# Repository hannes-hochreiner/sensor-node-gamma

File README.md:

# Sensor Node Gamma

## Core parts

### STM32
  * manufacturer: STMicroelectronics
  * manufacturer id: STM32L021K4T6
  * digi-key id: [497-17903-ND](https://www.digikey.de/product-detail/de/stmicroelectronics/STM32L021K4T6/497-17903-ND)
  * [datasheet](http://www.st.com/content/ccc/resource/technical/document/datasheet/86/a6/5f/95/33/50/4e/d6/DM00206858.pdf/files/DM00206858.pdf/jcr:content/translations/en.DM00206858.pdf)
  * sleep current: 0.54 µA
  * price: 1.87 EUR

### RFM98
  * manufacturer: Seeed Technology Co., Ltd
  * manufacturer id: 109990165
  * digi-key id: [1597-1491-ND](https://www.digikey.de/product-detail/de/seeed-technology-co-ltd/109990165/1597-1491-ND)
  * [datasheet](https://github.com/SeeedDocument/RFM95-98_LoRa_Module/blob/master/RFM95_96_97_98_DataSheet.pdf)
  * sleep current: 0.2 µA
  * price: 6.05 EUR

### sensor
  * manufacturer: Sensirion AG
  * manufacturer id: SHTC3
  * digi-key id: [1649-1105-1-ND](https://www.digikey.de/product-detail/de/sensirion-ag/SHTC3/1649-1105-1-ND/9477852)
  * [datasheet](https://media.digikey.com/pdf/Data%20Sheets/Sensirion%20PDFs/SHTC3_Prelim.pdf)
  * sleep current: 0.3 µA
  * price: 3.67 EUR

### antenna
  * manufacturer: Yageo
  * manufacturer id: ANT1204F002R0433A
  * digi-key id: [311-1570-1-ND](https://www.digikey.de/product-detail/de/yageo/ANT1204F002R0433A/311-1570-1-ND)
  * [datasheet](http://www.yageo.com/documents/recent/An_SMD_UHF_433_1204_0.pdf)
  * price: 1.38 EUR

## Power consumption

### Sleep

RFM:
7 ms @ 120 mA
rest @ 0.2 µA

(7 * 120 + 59993 * .0002) / 60000 = 0.0142 mA

STM32:
20 ms @ 2 mA
rest @ 1 µA

(20 * 2 + 59980 * 0.001) / 60000 = 0.0017 mA

SHTC3:
measuring: 12 ms @ 430 µA
idle: rest @ 0.3 µA

(12 * .43 + 59988 * 0.0003) / 60000 = 0.0004 mA

total: 0.0142 + 0.0017 + 0.0004 = 0.0163 mA

CR2032:
230 mAh

230 / 0.0163 = 14110 h = 588 d = 1.6 y

## Price

  * PCB: 7.50 EUR

price of the main components: 18.54 EUR

## Effort
  * system design: 1.5 h
  * circuit design: 2.5 h
  * pcb layout: 5.25 h
  * checks: 1.25 h

## TODOs
  * check all custom components and footprints

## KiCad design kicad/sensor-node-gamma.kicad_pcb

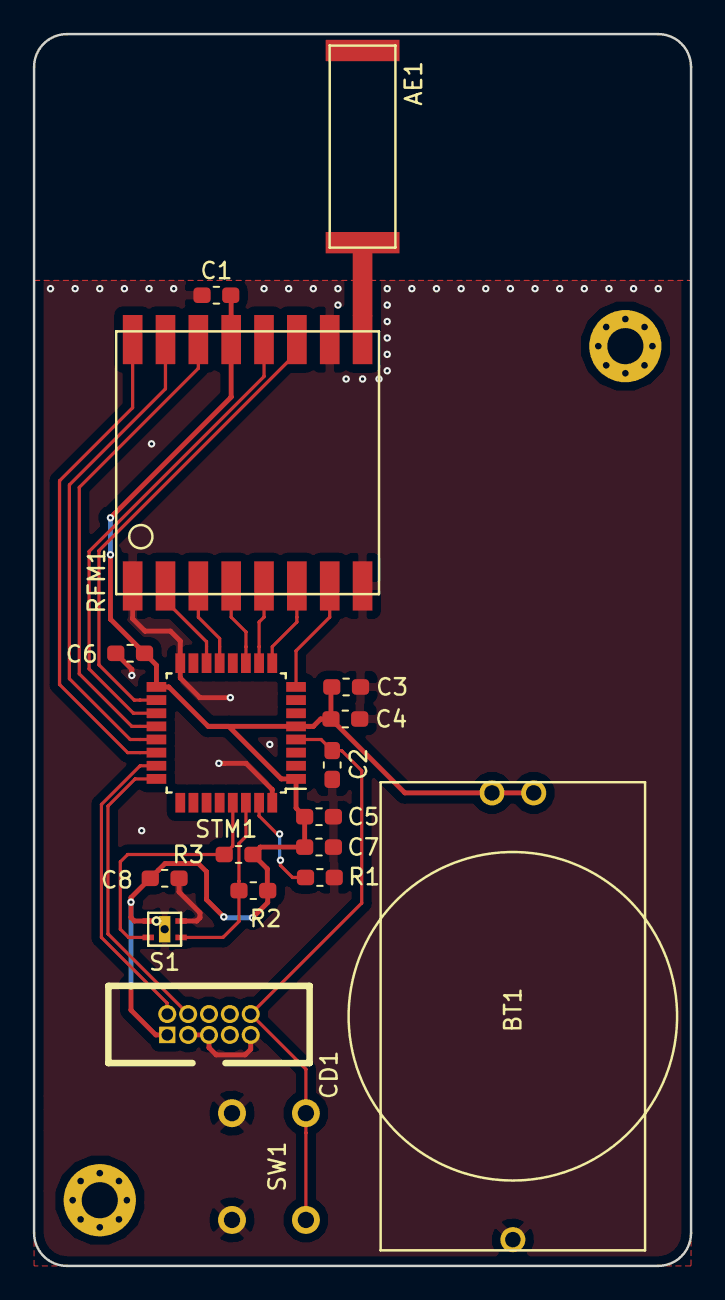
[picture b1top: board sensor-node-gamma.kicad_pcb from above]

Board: 2 copper layers, 40.0 x 75.0 mm, 18 parts (0 on the bottom side), 20 nets.

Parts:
AE1: Antenna; ANT1204F002R0433A
BT1: Custom_Battery; HU2032-LF
C1, C2, C4, C5, C6, C8: 0.1µF; C_0603_1608Metric_Pad1.05x0.95mm_HandSolder
C3: 1µF; C_0603_1608Metric_Pad1.05x0.95mm_HandSolder
C7: 10µF; C_0603_1608Metric_Pad1.05x0.95mm_HandSolder
CD1: CORTEX-DEBUG
R1, R2, R3: 10k; R_0603_1608Metric_Pad1.05x0.95mm_HandSolder
RFM1: RFM98
S1: SHTC3
STM1: STM32L021K4T6; LQFP-32_7x7mm_P0.8mm
SW1: SW_Push; switch

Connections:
/3V3: BT1.1, C1.1, C3.1, C4.1, C5.2, C6.1, C7.1, C8.1, CD1.1, R2.1, R3.2, RFM1.13, S1.1, STM1.1, STM1.5, STM1.17
/I2C_SCL: R3.1, S1.2, STM1.29
/I2C_SDA: R2.2, S1.3, STM1.30
/RFM_DIO0: RFM1.14, STM1.20
/RFM_DIO1: RFM1.15, STM1.21
/RFM_DIO2: RFM1.16, STM1.22
/RFM_DIO3: RFM1.11, STM1.18
/RFM_DIO4: RFM1.12, STM1.19
/RFM_DIO5: RFM1.7, STM1.8
/RFM_RESET: RFM1.6, STM1.9
/SPI_MISO: RFM1.2, STM1.14
/SPI_MOSI: RFM1.3, STM1.13
/SPI_NSS: RFM1.5, STM1.10
/SPI_SCK: RFM1.4, STM1.11
/SWD_CLK: CD1.4, STM1.24
/SWD_IO: CD1.2, STM1.23
/~SWD_RST: C2.1, CD1.10, STM1.4, SW1.2
GND: BT1.2, C1.2, C2.2, C3.2, C4.2, C5.1, C6.2, C7.2, C8.2, CD1.3, CD1.5, CD1.9, R1.1, RFM1.1, RFM1.8, RFM1.10, S1.4, STM1.16, STM1.32, SW1.1
unnamed: AE1.1, RFM1.9
unnamed: R1.2, STM1.31

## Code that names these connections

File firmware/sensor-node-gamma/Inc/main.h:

/* USER CODE BEGIN Header */
/**
  ******************************************************************************
  * @file           : main.h
  * @brief          : Header for main.c file.
  *                   This file contains the common defines of the application.
  ******************************************************************************
  ** This notice applies to any and all portions of this file
  * that are not between comment pairs USER CODE BEGIN and
  * USER CODE END. Other portions of this file, whether 
  * inserted by the user or by software development tools
  * are owned by their respective copyright owners.
  *
  * COPYRIGHT(c) 2018 STMicroelectronics
  *
  * Redistribution and use in source and binary forms, with or without modification,
  * are permitted provided that the following conditions are met:
  *   1. Redistributions of source code must retain the above copyright notice,
  *      this list of conditions and the following disclaimer.
  *   2. Redistributions in binary form must reproduce the above copyright notice,
  *      this list of conditions and the following disclaimer in the documentation
  *      and/or other materials provided with the distribution.
  *   3. Neither the name of STMicroelectronics nor the names of its contributors
  *      may be used to endorse or promote products derived from this software
  *      without specific prior written permission.
  *
  * THIS SOFTWARE IS PROVIDED BY THE COPYRIGHT HOLDERS AND CONTRIBUTORS "AS IS"
  * AND ANY EXPRESS OR IMPLIED WARRANTIES, INCLUDING, BUT NOT LIMITED TO, THE
  * IMPLIED WARRANTIES OF MERCHANTABILITY AND FITNESS FOR A PARTICULAR PURPOSE ARE
  * DISCLAIMED. IN NO EVENT SHALL THE COPYRIGHT HOLDER OR CONTRIBUTORS BE LIABLE
  * FOR ANY DIRECT, INDIRECT, INCIDENTAL, SPECIAL, EXEMPLARY, OR CONSEQUENTIAL
  * DAMAGES (INCLUDING, BUT NOT LIMITED TO, PROCUREMENT OF SUBSTITUTE GOODS OR
  * SERVICES; LOSS OF USE, DATA, OR PROFITS; OR BUSINESS INTERRUPTION) HOWEVER
  * CAUSED AND ON ANY THEORY OF LIABILITY, WHETHER IN CONTRACT, STRICT LIABILITY,
  * OR TORT (INCLUDING NEGLIGENCE OR OTHERWISE) ARISING IN ANY WAY OUT OF THE USE
  * OF THIS SOFTWARE, EVEN IF ADVISED OF THE POSSIBILITY OF SUCH DAMAGE.
  *
  ******************************************************************************
  */
/* USER CODE END Header */

/* Define to prevent recursive inclusion -------------------------------------*/
#ifndef __MAIN_H
#define __MAIN_H

#ifdef __cplusplus
extern "C" {
#endif

/* Includes ------------------------------------------------------------------*/
#include "stm32l0xx_hal.h"
#include "stm32l0xx_ll_crc.h"
#include "stm32l0xx.h"
#include "stm32l0xx_ll_i2c.h"
#include "stm32l0xx_ll_crs.h"
#include "stm32l0xx_ll_rcc.h"
#include "stm32l0xx_ll_bus.h"
#include "stm32l0xx_ll_system.h"
#include "stm32l0xx_ll_exti.h"
#include "stm32l0xx_ll_cortex.h"
#include "stm32l0xx_ll_utils.h"
#include "stm32l0xx_ll_pwr.h"
#include "stm32l0xx_ll_dma.h"
#include "stm32l0xx_ll_spi.h"
#include "stm32l0xx_ll_gpio.h"

/* Private includes ----------------------------------------------------------*/
/* USER CODE BEGIN Includes */
#include "rfm98_glue.h"
#include "message.h"
/* USER CODE END Includes */

/* Exported types ------------------------------------------------------------*/
/* USER CODE BEGIN ET */

/* USER CODE END ET */

/* Exported constants --------------------------------------------------------*/
/* USER CODE BEGIN EC */

/* USER CODE END EC */

/* Exported macro ------------------------------------------------------------*/
/* USER CODE BEGIN EM */

/* USER CODE END EM */

/* Exported functions prototypes ---------------------------------------------*/
void Error_Handler(void);

/* USER CODE BEGIN EFP */

/* USER CODE END EFP */

/* Private defines -----------------------------------------------------------*/
#define RFM_DIO5_Pin LL_GPIO_PIN_2
#define RFM_DIO5_GPIO_Port GPIOA
#define RFM_RESET_Pin LL_GPIO_PIN_3
#define RFM_RESET_GPIO_Port GPIOA
#define SPI1_NSS_Pin LL_GPIO_PIN_4
#define SPI1_NSS_GPIO_Port GPIOA
#define RFM_DIO3_Pin LL_GPIO_PIN_8
#define RFM_DIO3_GPIO_Port GPIOA
#define RFM_DIO4_Pin LL_GPIO_PIN_9
#define RFM_DIO4_GPIO_Port GPIOA
#define RFM_DIO0_Pin LL_GPIO_PIN_10
#define RFM_DIO0_GPIO_Port GPIOA
#define RFM_DIO1_Pin LL_GPIO_PIN_11
#define RFM_DIO1_GPIO_Port GPIOA
#define RFM_DIO2_Pin LL_GPIO_PIN_12
#define RFM_DIO2_GPIO_Port GPIOA
/* USER CODE BEGIN Private defines */

/* USER CODE END Private defines */

#ifdef __cplusplus
}
#endif

#endif /* __MAIN_H */

/************************ (C) COPYRIGHT STMicroelectronics *****END OF FILE****/

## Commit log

2018-09-02 initial design commit
2018-09-02 changes antenna footprint
2018-09-02 updated effort
2018-09-04 updated to kicad 5
2018-09-06 re-routed pcb
2018-09-07 re-rerouted pcb
2018-09-07 updated effort times
2018-09-10 added cap for sensor
2018-09-10 updated efforts
2018-09-12 updated design rules and ran check
2018-09-14 added prices
2018-09-14 switched to more easily available parts
2018-09-15 exchanged radio and sensor in schematic
2018-09-15 added footprints
2018-09-15 added new antenna
2018-09-15 update PCB
2018-09-15 updated PCB
2018-09-15 added better pin 1 marks
2018-10-02 sensor working
2018-10-02 removed pointer calculation
2018-10-03 added sending of test message
2018-10-03 updated transmission parameters
2018-10-04 added chip config
2018-10-06 updated transmission handling
2018-10-06 changed sensor description
2018-10-07 completed hybrid version
2018-10-27 started work on the case
2018-10-27 firmware template
2018-10-27 snapshot
2018-10-27 communication with sensor and radio established
2018-11-04 switched to using LL libs for I2C
2018-11-25 introduced a new message format
2018-11-25 added crc check of sensor values
2018-11-25 added readout of sensor id
2018-11-25 added encryption
2018-12-17 upgraded to new version of cubemx
2018-12-29 updated lifetime calculations
